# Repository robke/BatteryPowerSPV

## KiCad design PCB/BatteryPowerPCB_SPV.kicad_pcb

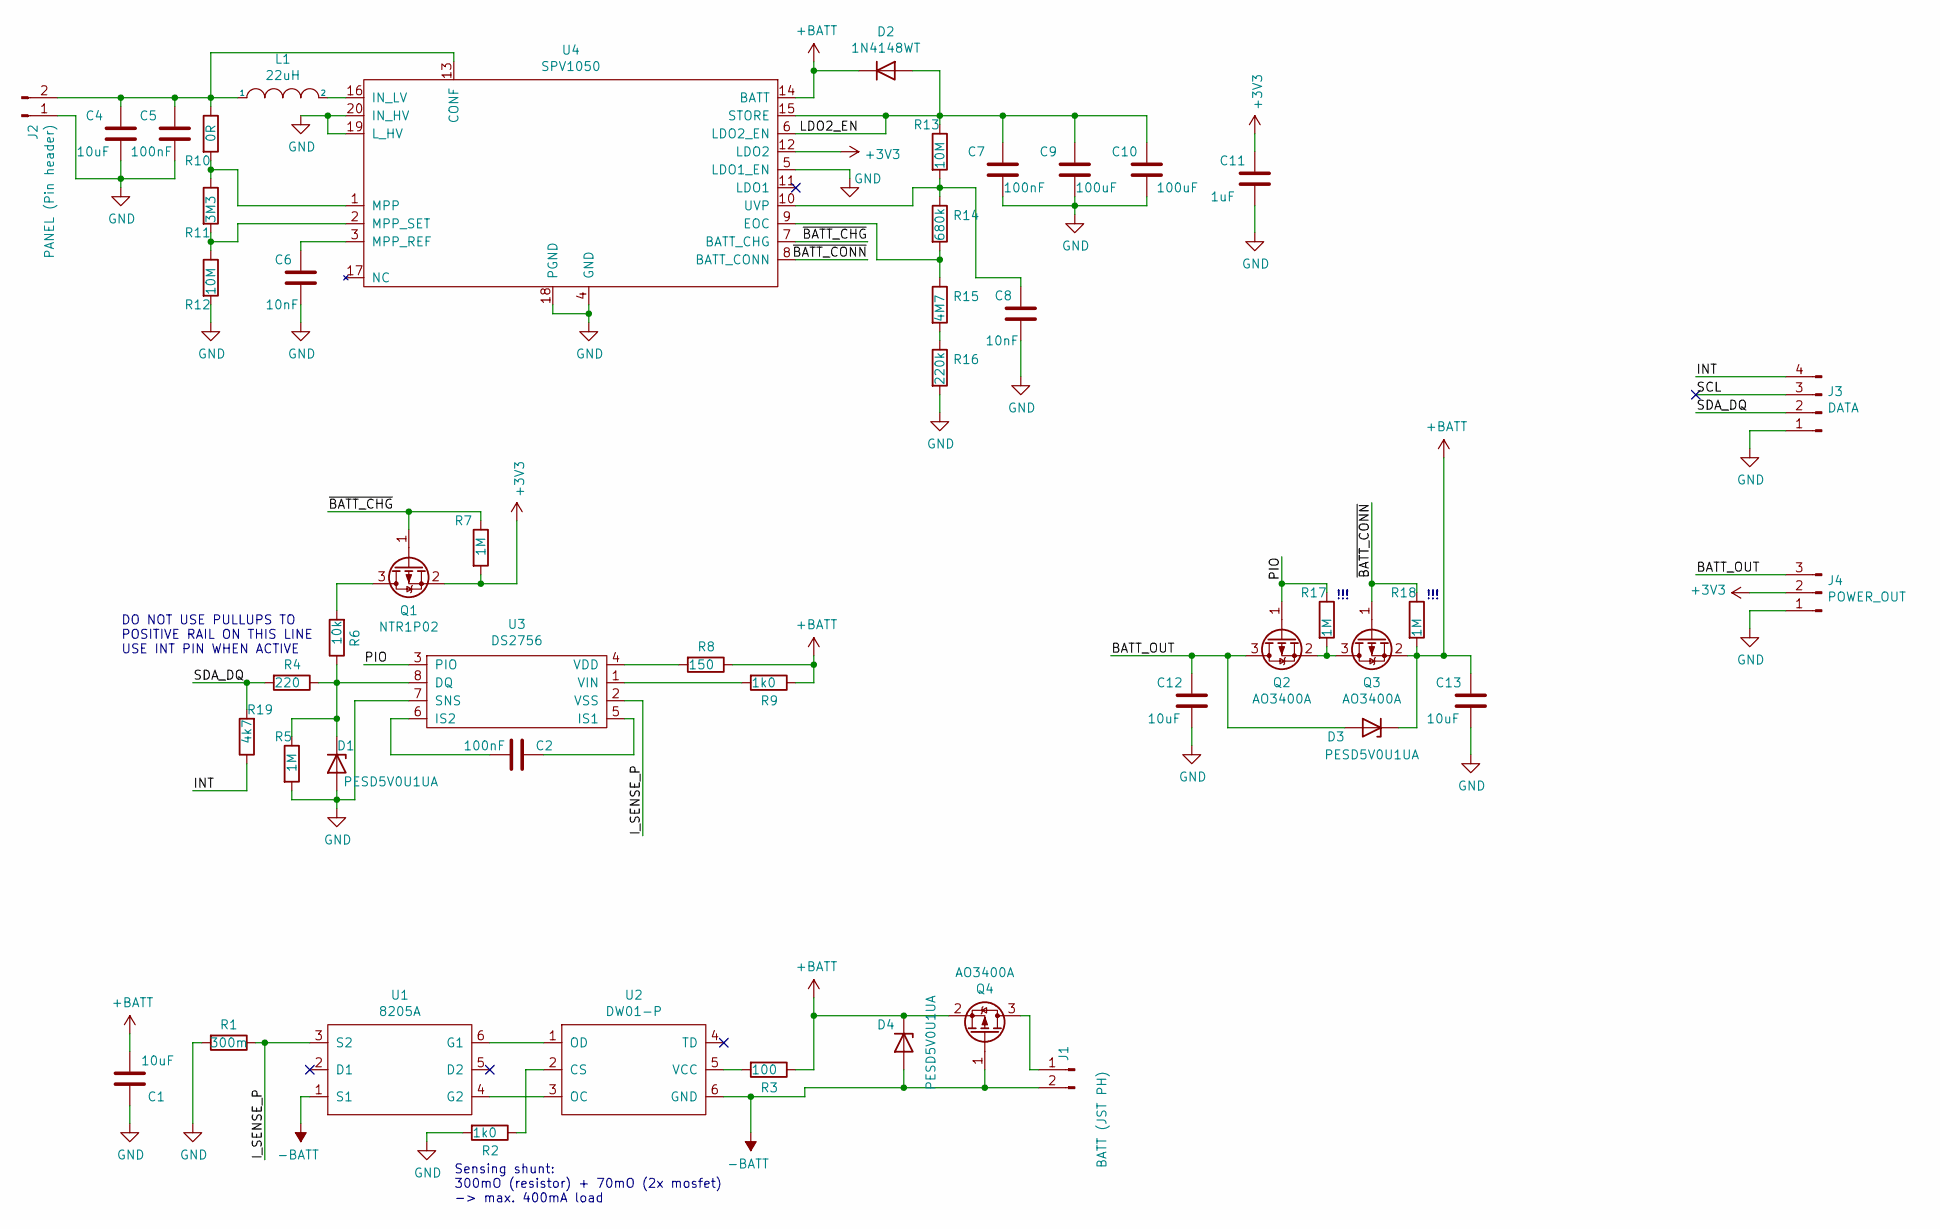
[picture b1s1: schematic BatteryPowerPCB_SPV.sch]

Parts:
C1, C4, C12, C13: 10uF; C_0603_1608Metric_Pad1.08x0.95mm_HandSolder; LCSC C19702
C2, C5, C7: 100nF; C_0603_1608Metric_Pad1.08x0.95mm_HandSolder; LCSC C14663
C6, C8: 10nF; C_0603_1608Metric_Pad1.08x0.95mm_HandSolder; LCSC C57112
C9, C10: 100uF; C_0805_2012Metric_Pad1.18x1.45mm_HandSolder; LCSC C15355
C11: 1uF; C_0603_1608Metric_Pad1.08x0.95mm_HandSolder; LCSC C15849
D1, D3, D4: PESD5V0U1UA; D_SOD-323_HandSoldering; LCSC C139614
D2: 1N4148WT; D_SOD-523; LCSC C511874
J1: BATT (JST PH); JST_PH_S2B-PH-K_1x02_P2.00mm_Horizontal
J2: PANEL (Pin header); PinHeader_1x02_P2.54mm_Vertical
J3: DATA; JST_PH_S4B-PH-K_1x04_P2.00mm_Horizontal
J4: POWER_OUT; JST_PH_S3B-PH-K_1x03_P2.00mm_Horizontal
L1: 22uH; L_0805_2012Metric_Pad1.15x1.40mm_HandSolder
Q1: NTR1P02; SOT-23
Q2, Q3, Q4: AO3400A; SOT-23
R1: 300m; R_1206_3216Metric_Pad1.30x1.75mm_HandSolder
R2, R9: 1k0; R_0603_1608Metric_Pad0.98x0.95mm_HandSolder
R3: 100; R_0603_1608Metric_Pad0.98x0.95mm_HandSolder
R4: 220; R_0603_1608Metric_Pad0.98x0.95mm_HandSolder; LCSC C22962
R5, R7, R17, R18: 1M; R_0603_1608Metric_Pad0.98x0.95mm_HandSolder
R6: 10k; R_0603_1608Metric_Pad0.98x0.95mm_HandSolder
R8: 150; R_0603_1608Metric_Pad0.98x0.95mm_HandSolder
R10: 0R; R_0603_1608Metric_Pad0.98x0.95mm_HandSolder
R11: 3M3; R_0603_1608Metric_Pad0.98x0.95mm_HandSolder
R12, R13: 10M; R_0603_1608Metric_Pad0.98x0.95mm_HandSolder
R14: 680k; R_0603_1608Metric_Pad0.98x0.95mm_HandSolder
R15: 4M7; R_0603_1608Metric_Pad0.98x0.95mm_HandSolder
R16: 220k; R_0603_1608Metric_Pad0.98x0.95mm_HandSolder
R19: 4k7; R_0603_1608Metric_Pad0.98x0.95mm_HandSolder; LCSC C22962
U1: 8205A; SOT-23-6_Handsoldering
U2: DW01-P; SOT-23-6_Handsoldering
U3: DS2756; TSSOP-8_4.4x3mm_P0.65mm
U4: SPV1050; QFN-20_3x3

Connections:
+3V3: C11.1, J4.2, Q1.2 (S), R7.2, U4.12 (LDO2)
+BATT: C1.2, C13.1, D2.1 (K), D3.1 (K), D4.1 (K), Q3.2 (S), Q4.2 (S), R3.1, R8.1, R9.1, R18.2, U4.14 (BATT)
-BATT: D4.2 (A), J1.2, Q4.1 (G), U1.1 (S1), U2.6 (GND)
/BATT_OUT: C12.1, D3.2 (A), J4.3, Q2.3 (D)
/INT: J3.4, R19.1
/I_SENSE_P: R1.1, U1.3 (S2), U3.2 (VSS)
/LDO2_EN: C7.1, C9.1, C10.1, D2.2 (A), R13.1, U4.6 (LDO2_EN), U4.15 (STORE)
/PIO: Q2.1 (G), R17.1, U3.3 (PIO)
/SCL: J3.3
/SDA_DQ: J3.2, R4.2, R19.2
/~BATT_CHG: Q1.1 (G), R7.1, U4.7 (BATT_CHG)
/~BATT_CONN: Q3.1 (G), R18.1, U4.8 (BATT_CONN)
GND: C1.1, C4.2, C5.2, C6.2, C7.2, C8.2, C9.2, C10.2, C11.2, C12.2, C13.2, D1.2 (A), J2.1, J3.1, J4.1, R1.2, R2.2, R5.2, R12.2, R16.2, U3.7 (SNS), U4.4 (GND), U4.5 (LDO1_EN), U4.18 (PGND), U4.19 (L_HV), U4.20 (IN_HV)
unnamed: C2.1, U3.5 (IS1)
unnamed: C2.2, U3.6 (IS2)
unnamed: C4.1, C5.1, J2.2, L1.1, R10.1, U4.13 (CONF)
unnamed: C6.1, U4.3 (MPP_REF)
unnamed: C8.1, R13.2, R14.1, U4.10 (UVP)
unnamed: D1.1 (K), R4.1, R5.1, R6.1, U3.8 (DQ)
unnamed: J1.1, Q4.3 (D)
unnamed: L1.2, U4.16 (IN_LV)
unnamed: Q1.3 (D), R6.2
unnamed: Q2.2 (S), Q3.3 (D), R17.2
unnamed: R2.1, U2.2 (CS)
unnamed: R3.2, U2.5 (VCC)
unnamed: R8.2, U3.4 (VDD)
unnamed: R9.2, U3.1 (VIN)
unnamed: R10.2, R11.1, U4.1 (MPP)
unnamed: R11.2, R12.1, U4.2 (MPP_SET)
unnamed: R14.2, R15.1, U4.9 (EOC)
unnamed: R15.2, R16.1
unnamed: U1.4 (G2), U2.3 (OC)
unnamed: U1.6 (G1), U2.1 (OD)

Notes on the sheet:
DO NOT USE PULLUPS TO POSITIVE RAIL ON THIS LINE USE INT PIN WHEN ACTIVE
!!!
Sensing shunt: 300mO (resistor) + 70mO (2x mosfet) -> max. 400mA load

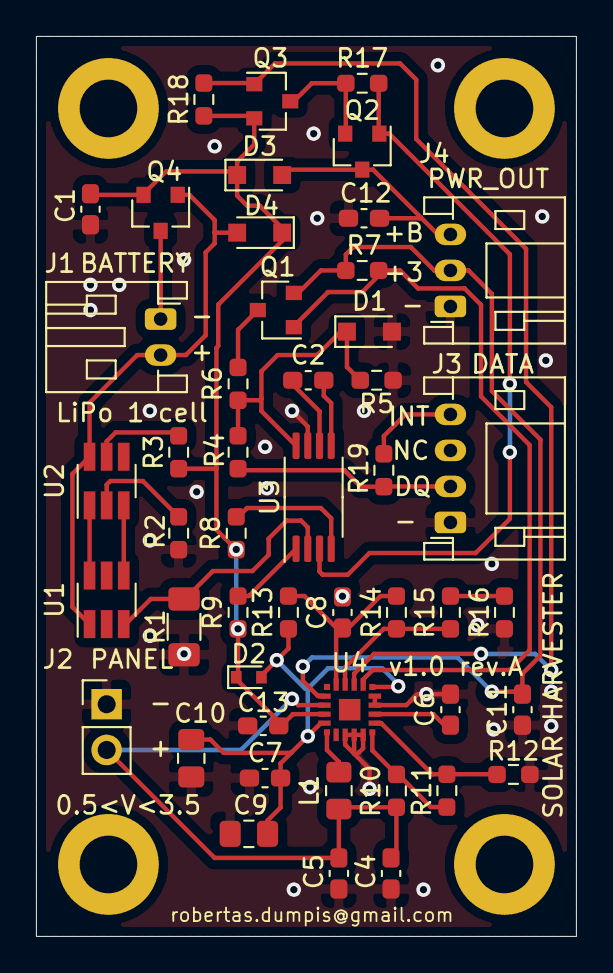
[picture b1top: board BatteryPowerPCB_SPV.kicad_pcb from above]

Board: 2 copper layers, 30.0 x 50.0 mm, 48 parts (0 on the bottom side), 32 nets.

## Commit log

2023-06-28 Initial PCB version
